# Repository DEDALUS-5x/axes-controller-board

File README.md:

# Axes Controller Board (ACB)

KiCad design files of the Axes Controller Board, the STM32H723-based motion
controller of the [DEDALUS](https://dedalus-5x.github.io/dedalus-docs/)
five-axis printer. The board drives two brushed DC servo axes through
external H-bridges and six stepper drivers in StepStick sockets, reads
differential incremental and SPI absolute encoders, and carries a
Raspberry Pi 5 as a daughterboard.

Current revision: 1.1.0 (see [Revision history](#revision-history)).

Firmware: <https://github.com/DEDALUS-5x/axes-controller-fw>

## Contents

| File | Description |
| --- | --- |
| `axes-controller-board.kicad_pro` | KiCad 8 project |
| `axes-controller-board.kicad_sch`, `mcu.kicad_sch`, `sensors.kicad_sch` | Schematics (root, MCU, sensors) |
| `axes-controller-board.kicad_pcb` | Four-layer layout, 203 x 108 mm, 1.6 mm |
| `libs/footprints.pretty/` | Footprints that can be redistributed with the design |
| `sym-lib-table` | Project symbol libraries (third-party, see below) |
| `outputs/ACB_schematic.pdf` | Schematic, PDF |
| `outputs/ACB_gerbers.zip` | Gerber and Excellon drill files (four layers) |
| `outputs/ACB_bom.csv` | BOM of the SMT-assembled parts, with LCSC codes |
| `outputs/ACB_positions.csv` | Placement of the SMT-assembled parts (top side, mm) |

The files in `outputs/` were exported from the KiCad project with `kicad-cli`
(KiCad 9). For JLCPCB assembly, the
[Fabrication Toolkit](https://github.com/bennymeg/Fabrication-Toolkit) plug-in
generates the BOM and placement files in the required format, using the LCSC
codes and rotation offsets stored in the schematic.

## Third-party library parts

The symbols, footprints and 3D models of the parts below are SamacSys ECAD
models or vendor models. Their terms allow using them in board designs
without restriction, but not redistributing them as library components, so
they are not included in this repository.

The schematics and the PCB embed a copy of every symbol and footprint they
use: the project opens and fabrication outputs can be generated without these
libraries. Download them only to edit the parts, free of charge, and place them
at the paths below, which match `sym-lib-table` and the footprint names in the
layout.

| Part | Use | Expected location | Source |
| --- | --- | --- | --- |
| STM32H723ZGT6 | IC5, microcontroller | `libs/STM32H7/STM32H723ZGT6/` | [Component Search Engine](https://componentsearchengine.com) (SamacSys) |
| TPS5450QDDARQ1 | IC1, 5 V buck converter | `libs/TPS5450/` | [Component Search Engine](https://componentsearchengine.com) (SamacSys) |
| ACS37800KMACTR-030B3-SPI | IC2, IC3, current monitors (optional) | `libs/ACS/` | [Component Search Engine](https://componentsearchengine.com) (SamacSys) |
| Phoenix Contact 1985205, 1985234, 1985250 | Terminal blocks | `libs/morsetto/`, `libs/footprints.pretty/`, `libs/3dmodels/` | [Component Search Engine](https://componentsearchengine.com) (SamacSys) |
| Samtec FTSH-107-01-L-DV-K-TR | J1, STDC14 debug connector | `libs/footprints.pretty/` | [Samtec](https://www.samtec.com) |
| Raspberry Pi 4 Model B | 3D model only | `libs/3dmodels/` | [Raspberry Pi Ltd](https://www.raspberrypi.com) |

## Revision history

### 1.1.0

The layout matches the firmware
([axes-controller-fw](https://github.com/DEDALUS-5x/axes-controller-fw)):
no hand modifications are needed.

- The STEP lines of five driver sockets go to timer outputs, so that steps are
  generated in hardware: Z1 on PB9 (TIM17 CH1), Z2 on PB5 (TIM3 CH2), A1 on PC12
  (TIM15 CH1), A2 on PB6 (TIM16 CH1N), C on PC7 (TIM8 CH2). The 33 ohm series
  resistors are kept; R19 and R23 moved next to the new routes, R4 took the
  place of R27.
- The Raspberry Pi chip select (J27 pin 24) goes to PA4, the hardware NSS of
  SPI3.
- The third DC-servo channel is removed (terminal J4, resistors R27 and R28),
  together with its current monitor IC4, capacitor C39 and supply terminal J30.
- New connector J47 (1x8, 2.54 mm) for an SPI absolute encoder on SPI4, chip
  select PC15. Same pinout as J31 and J32: 1-2 3V3, 3 not connected, 4 CS,
  5 SCK, 6 MOSI, 7 MISO, 8 GND.
- Spare header J5: pins 6 and 7 are no longer connected (PB5 and PB6 are STEP
  lines now); six spare I/O remain.

### 1.0.0 (prototype)

On the 1.0.0 board the following signals must be re-routed with wires, because
the STEP lines of five driver sockets reach pins without timer outputs and the
Raspberry Pi chip select reaches a pin without the SPI3 hardware NSS function.
The firmware uses the re-routed pins. On this revision the third DC-servo
channel loses one PWM line (PC7 is used for STEP C).

| Signal | Destination | Routed to | Re-routed to |
| --- | --- | --- | --- |
| STEP Z1 | J9 pin 7 | PE0 | PB9 (TIM17 CH1) |
| STEP Z2 | J12 pin 7 | PE3 | PB5 (TIM3 CH2), J5 pin 7 |
| STEP A1 | J15 pin 7 | PD0 | PC12 (TIM15 CH1) |
| STEP A2 | J18 pin 7 | PD3 | PB6 (TIM16 CH1N), J5 pin 6 |
| STEP C | J21 pin 7 | PD11 | PC7 (TIM8 CH2), J4 pin 2 |
| Raspberry Pi CE0 | J27 pin 24 | PB1 | PA4 (SPI3 NSS) |

## License

Copyright 2026 Leonardo Pasquato.

This source describes Open Hardware and is licensed under the CERN-OHL-S v2.

You may redistribute and modify this source and make products using it under
the terms of the CERN-OHL-S v2 (<https://ohwr.org/cern_ohl_s_v2.txt>).

This source is distributed WITHOUT ANY EXPRESS OR IMPLIED WARRANTY,
INCLUDING OF MERCHANTABILITY, SATISFACTORY QUALITY AND FITNESS FOR A
PARTICULAR PURPOSE. Please see the CERN-OHL-S v2 for applicable conditions.

Source location: <https://github.com/DEDALUS-5x/axes-controller-board>

As per CERN-OHL-S v2 section 4, should You produce hardware based on this
source, You must where practicable maintain the Source Location visible on
the external case of the Gizmo or other products you make using this source.

Exceptions: `libs/footprints.pretty/MountingHole_3.2mm_M3_ISO14580.kicad_mod`
and `libs/footprints.pretty/raspberrypi.kicad_mod` are derived from the
[KiCad libraries](https://www.kicad.org/libraries/license/) and remain under
CC-BY-SA 4.0 with the KiCad library exception.

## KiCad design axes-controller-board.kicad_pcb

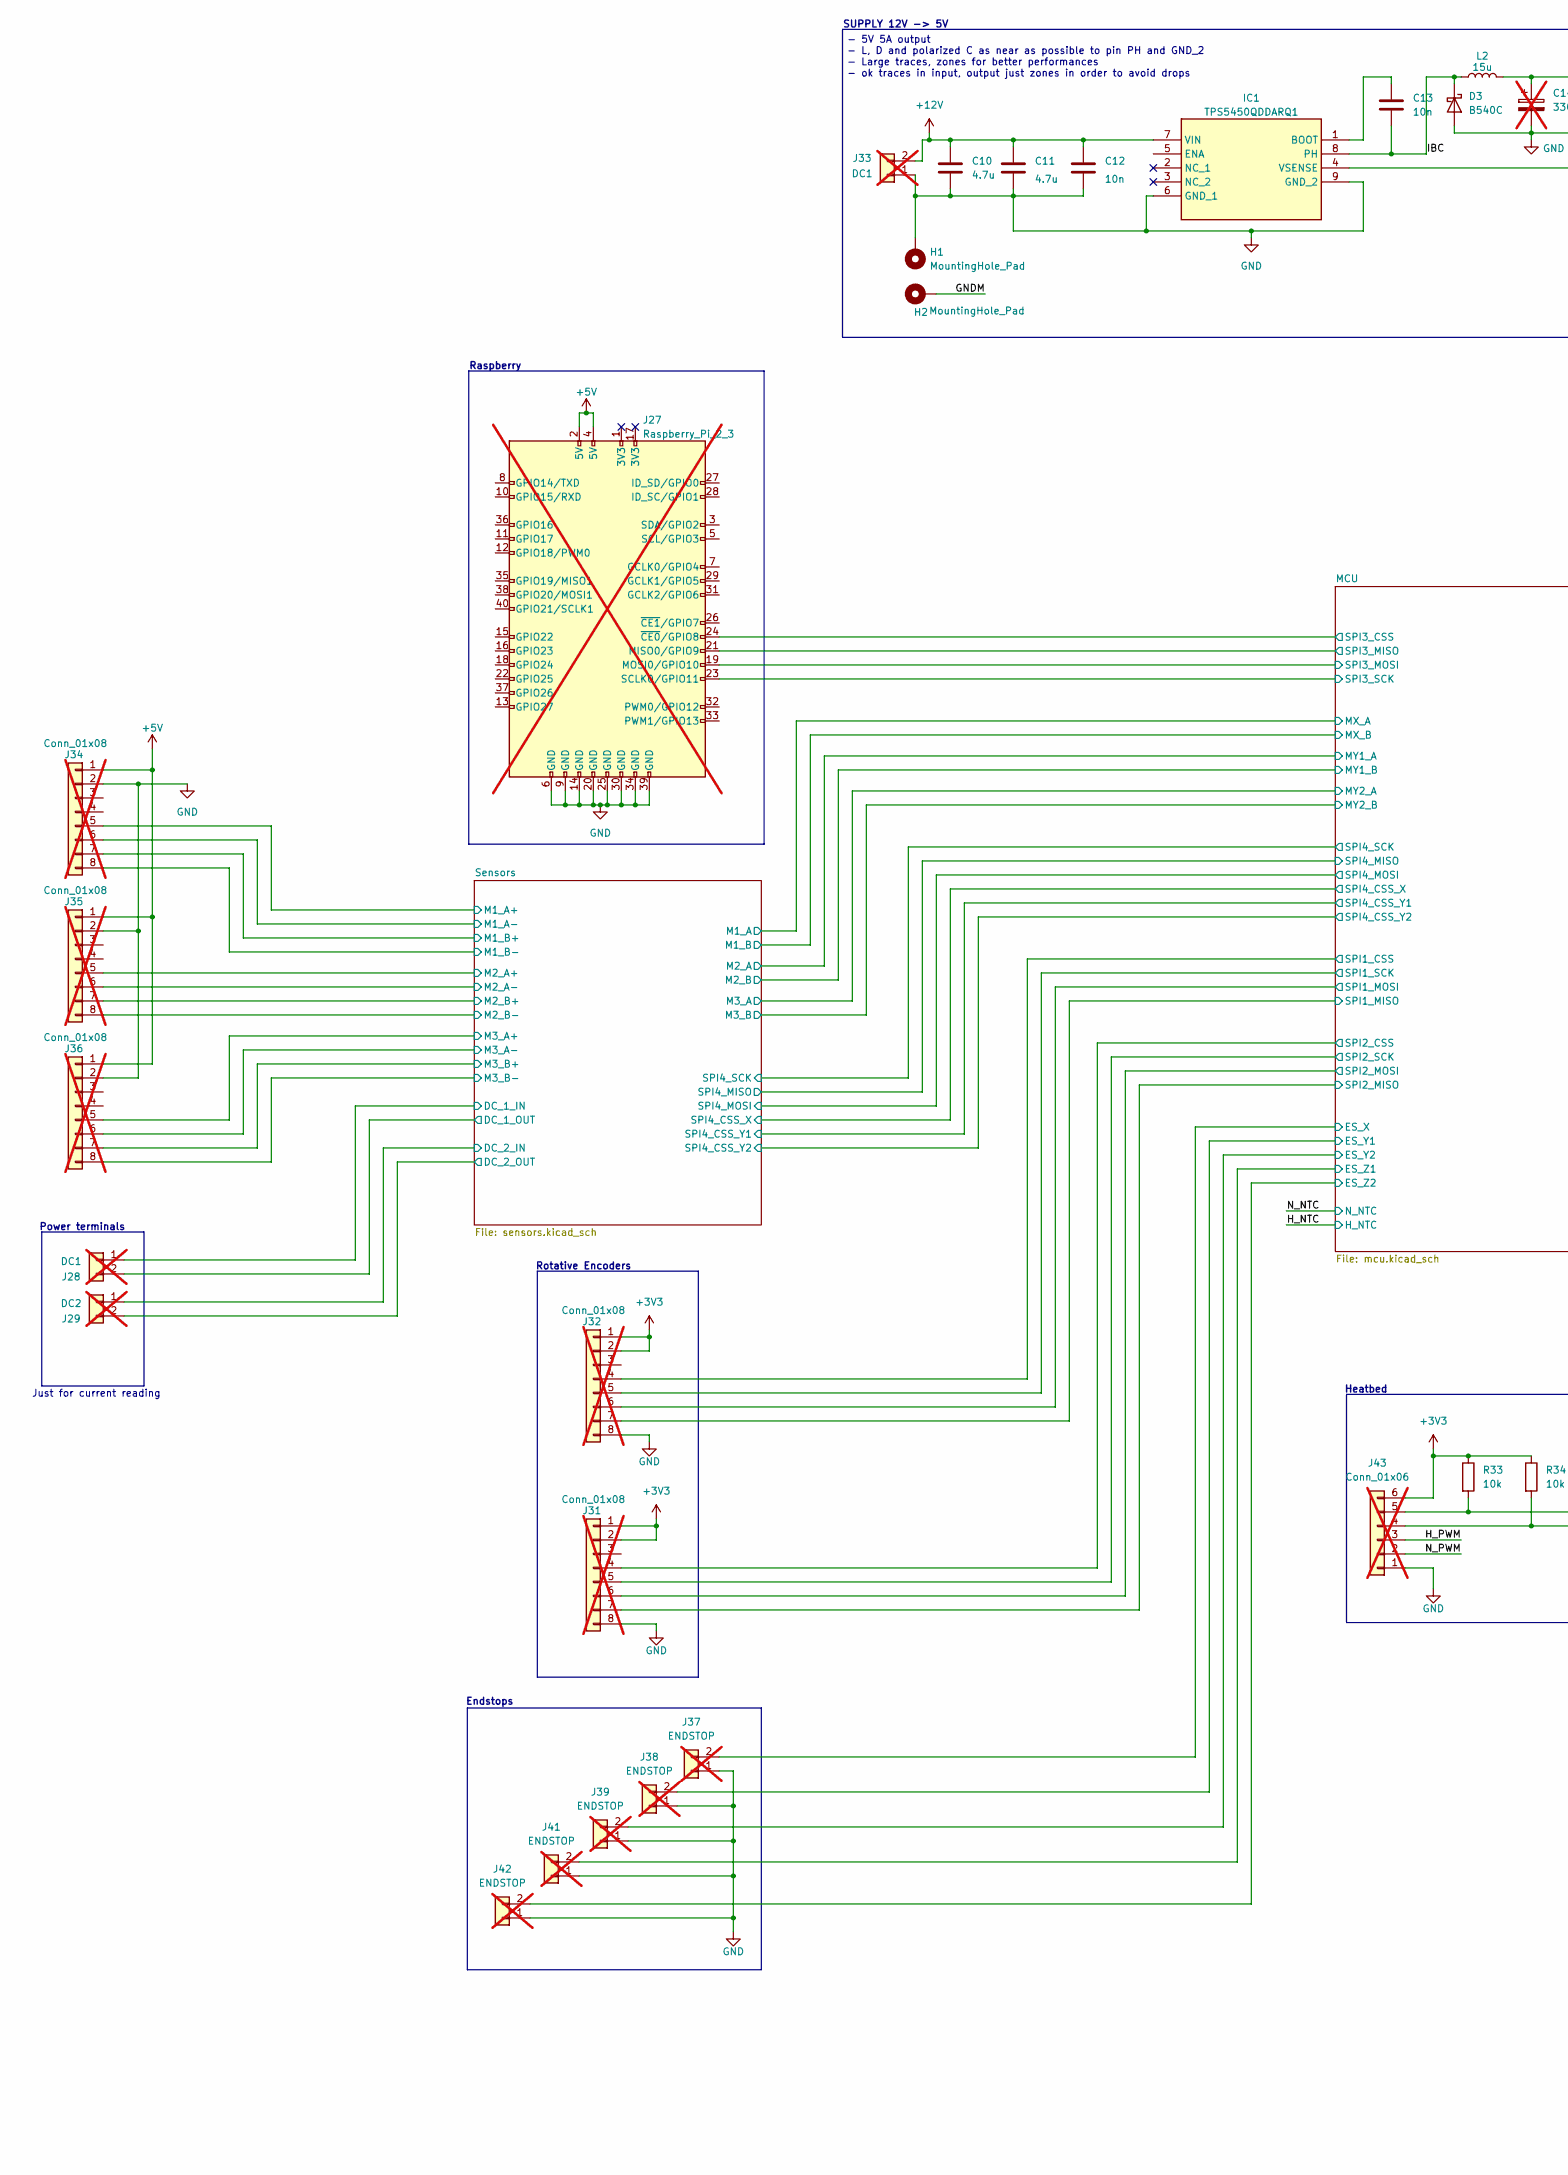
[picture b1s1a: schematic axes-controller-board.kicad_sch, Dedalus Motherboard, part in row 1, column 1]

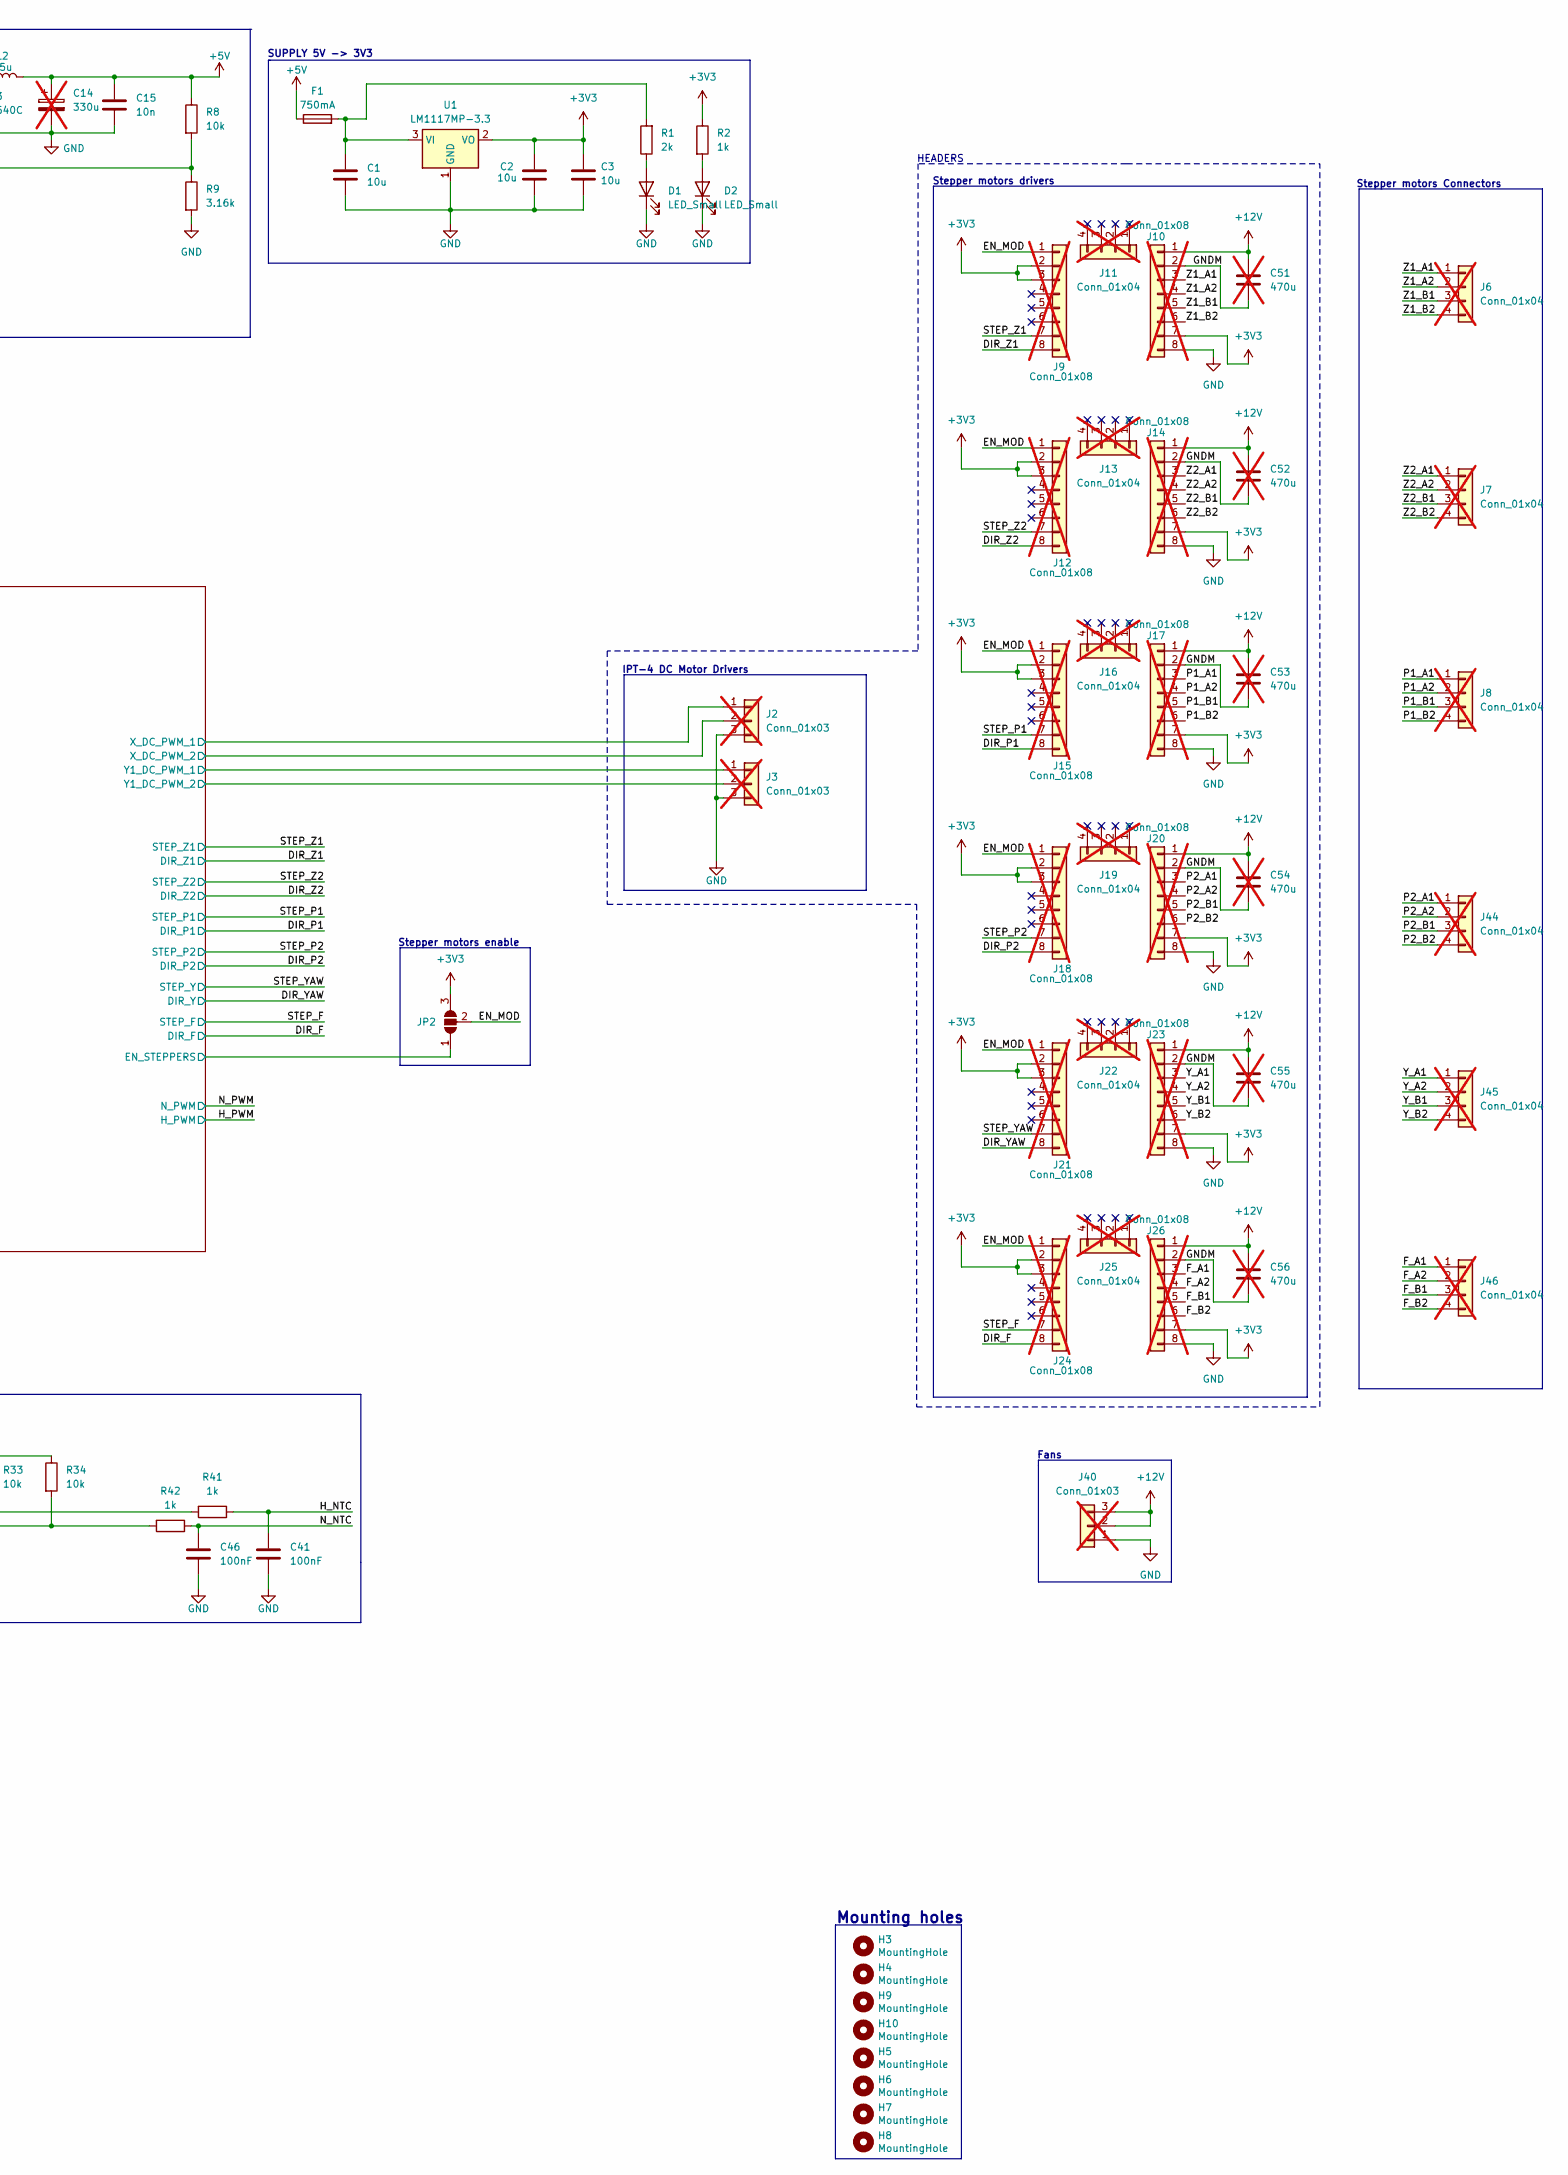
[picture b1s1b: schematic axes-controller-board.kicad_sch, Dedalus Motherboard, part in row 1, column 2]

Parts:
C1, C2, C3: 10u; C_0603_1608Metric; LCSC C19702
C10, C11: 4.7u; C_0805_2012Metric; LCSC C1779
C12, C13, C15: 10n; C_0603_1608Metric; LCSC C57112
C14: 330u; CP_Radial_D10.0mm_P5.00mm; not fitted
C41, C46: 100nF; C_0603_1608Metric; LCSC C14663
C51, C52, C53, C54, C55, C56: 470u; PinHeader_1x02_P1.00mm_Vertical; not fitted
D1, D2: LED_Small; D_0603_1608Metric; MPN TLMS1000-GS15; LCSC C2286
D3: B540C; D_SMC_Handsoldering; LCSC C72264
F1: 750mA; Fuse_0603_1608Metric; LCSC C206991
H1, H2: MountingHole_Pad; TestPoint_GNDedge
H3, H4, H5, H6, H7, H8, H9, H10: MountingHole; MountingHole_3.2mm_M3_ISO14580
IC1: TPS5450QDDARQ1; SOIC127P600X170-9N; Mouser Part Number 595-TPS5450QDDARQ1
J2, J3, J40: Conn_01x03; 1985205; not fitted
J6, J7, J8, J44, J45, J46: Conn_01x04; JST_XH_B4B-XH-A_1x04_P2.50mm_Vertical; not fitted
J9, J10, J12, J14, J15, J17, J18, J20, J21, J23, J24, J26: Conn_01x08; PinHeader_1x08_P2.54mm_Vertical; not fitted
J11, J13, J16, J19, J22, J25: Conn_01x04; PinHeader_1x04_P2.54mm_Vertical; not fitted
J27: Raspberry_Pi_2_3; raspberrypi; MPN 2.54-2*20; LCSC C2977589; not fitted
J28, J33: DC1; TerminalBlock_Phoenix_MKDS-1,5-2-5.08_1x02_P5.08mm_Horizont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; not fitted
J29: DC2; TerminalBlock_Phoenix_MKDS-1,5-2-5.08_1x02_P5.08mm_Horizont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; not fitted
J31, J32, J34, J35, J36: Conn_01x08; 1985250; not fitted
J37, J38, J39, J41, J42: ENDSTOP; PinHeader_1x02_P2.54mm_Vertical; not fitted
J43: Conn_01x06; 1985234; not fitted
JP2: SolderJumper_3_Open; SolderJumper-3_P1.3mm_Open_RoundedPad1.0x1.5mm
L2: 15u; L_12x12mm_H6mm; LCSC C2847584
R1: 2k; R_0603_1608Metric; LCSC C22975
R2, R41, R42: 1k; R_0603_1608Metric; LCSC C21190
R8, R33, R34: 10k; R_0603_1608Metric; LCSC C25804
R9: 3.16k; R_0603_1608Metric; LCSC C100959
U1: LM1117MP-3.3; SOT-223-3_TabPin2; MPN LM1117MP-3.3/TR; LCSC C498153

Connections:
+3V3: C2.1, C3.1, J9.2, J9.3, J10.7, J12.2, J12.3, J14.7, J15.2, J15.3, J17.7, J18.2, J18.3, J20.7, J21.2, J21.3, J23.7, J24.2, J24.3, J26.7, J31.1, J31.2, J32.1, J32.2, J43.6, JP2.3 (B), R2.1, R33.1, R34.1, U1.2 (VO); also elsewhere on the board
+5V: C14.1, C15.1, F1.1, J27.2 (5V), J27.4 (5V), J34.1, J35.1, J36.1, L2.2, R8.1; also elsewhere on the board
+12V: C10.1, C11.1, C12.1, C51.1, C52.1, C53.1, C54.1, C55.1, C56.1, IC1.7 (VIN), J10.1, J14.1, J17.1, J20.1, J23.1, J26.1, J33.2, J40.2, J40.3
/DIR_F: J24.8; also elsewhere on the board
/DIR_P1: J15.8; also elsewhere on the board
/DIR_P2: J18.8; also elsewhere on the board
/DIR_YAW: J21.8; also elsewhere on the board
/DIR_Z1: J9.8; also elsewhere on the board
/DIR_Z2: J12.8; also elsewhere on the board
/EN_MOD: J9.1, J12.1, J15.1, J18.1, J21.1, J24.1, JP2.2 (C)
/F_A1: J26.3, J46.1
/F_A2: J26.4, J46.2
/F_B1: J26.5, J46.3
/F_B2: J26.6, J46.4
/GNDM: C51.2, C52.2, C53.2, C54.2, C55.2, C56.2, H2.1, J10.2, J14.2, J17.2, J20.2, J23.2, J26.2
/H_NTC: C41.1, R41.1; also elsewhere on the board
/H_PWM: J43.3; also elsewhere on the board
/IBC: C13.1, D3.1 (K), IC1.8 (PH), L2.1
/MCU/EN_STEPPERS: JP2.1 (A); also elsewhere on the board
/MCU/ES_X: J37.2; also elsewhere on the board
/MCU/ES_Y1: J38.2; also elsewhere on the board
/MCU/ES_Y2: J39.2; also elsewhere on the board
/MCU/ES_Z1: J41.2; also elsewhere on the board
/MCU/ES_Z2: J42.2; also elsewhere on the board
/MCU/SPI1_CSS: J32.4; also elsewhere on the board
/MCU/SPI1_MISO: J32.7; also elsewhere on the board
/MCU/SPI1_MOSI: J32.6; also elsewhere on the board
/MCU/SPI1_SCK: J32.5; also elsewhere on the board
/MCU/SPI2_CSS: J31.4; also elsewhere on the board
/MCU/SPI2_MISO: J31.7; also elsewhere on the board
/MCU/SPI2_MOSI: J31.6; also elsewhere on the board
/MCU/SPI2_SCK: J31.5; also elsewhere on the board
/MCU/SPI3_CSS: J27.24 (~CE0/GPIO8); also elsewhere on the board
/MCU/SPI3_MISO: J27.21 (MISO0/GPIO9); also elsewhere on the board
/MCU/SPI3_MOSI: J27.19 (MOSI0/GPIO10); also elsewhere on the board
/MCU/SPI3_SCK: J27.23 (SCLK0/GPIO11); also elsewhere on the board
/MCU/X_DC_PWM_1: J2.1; also elsewhere on the board
/MCU/X_DC_PWM_2: J2.2; also elsewhere on the board
/MCU/Y1_DC_PWM_1: J3.1; also elsewhere on the board
/MCU/Y1_DC_PWM_2: J3.2; also elsewhere on the board
/N_NTC: C46.1, R42.1; also elsewhere on the board
/N_PWM: J43.2; also elsewhere on the board
/P1_A1: J8.1, J17.3
/P1_A2: J8.2, J17.4
/P1_B1: J8.3, J17.5
/P1_B2: J8.4, J17.6
/P2_A1: J20.3, J44.1
/P2_A2: J20.4, J44.2
/P2_B1: J20.5, J44.3
/P2_B2: J20.6, J44.4
/STEP_F: J24.7; also elsewhere on the board
/STEP_P1: J15.7; also elsewhere on the board
/STEP_P2: J18.7; also elsewhere on the board
/STEP_YAW: J21.7; also elsewhere on the board
/STEP_Z1: J9.7; also elsewhere on the board
/STEP_Z2: J12.7; also elsewhere on the board
/Sensors/DC_1_IN: J28.1; also elsewhere on the board
/Sensors/DC_1_OUT: J28.2; also elsewhere on the board
/Sensors/DC_2_IN: J29.1; also elsewhere on the board
/Sensors/DC_2_OUT: J29.2; also elsewhere on the board
/Sensors/M1_A+: J34.5; also elsewhere on the board
/Sensors/M1_A-: J34.6; also elsewhere on the board
/Sensors/M1_B+: J34.7; also elsewhere on the board
/Sensors/M1_B-: J34.8; also elsewhere on the board
/Sensors/M2_A+: J35.5; also elsewhere on the board
/Sensors/M2_A-: J35.6; also elsewhere on the board
/Sensors/M2_B+: J35.7; also elsewhere on the board
/Sensors/M2_B-: J35.8; also elsewhere on the board
/Sensors/M3_A+: J36.5; also elsewhere on the board
/Sensors/M3_A-: J36.6; also elsewhere on the board
/Sensors/M3_B+: J36.7; also elsewhere on the board
/Sensors/M3_B-: J36.8; also elsewhere on the board
/Y_A1: J23.3, J45.1
/Y_A2: J23.4, J45.2
/Y_B1: J23.5, J45.3
/Y_B2: J23.6, J45.4
/Z1_A1: J6.1, J10.3
/Z1_A2: J6.2, J10.4
/Z1_B1: J6.3, J10.5
/Z1_B2: J6.4, J10.6
/Z2_A1: J7.1, J14.3
/Z2_A2: J7.2, J14.4
/Z2_B1: J7.3, J14.5
/Z2_B2: J7.4, J14.6
GND: C1.2, C2.2, C3.2, C10.2, C11.2, C12.2, C14.2, C15.2, C41.2, C46.2, D1.1 (K), D2.1 (K), D3.2 (A), H1.1, IC1.6 (GND_1), IC1.9 (GND_2), J2.3, J3.3, J10.8, J14.8, J17.8, J20.8, J23.8, J26.8, J27.6 (GND), J27.9 (GND), J27.14 (GND), J27.20 (GND), J27.25 (GND), J27.30 (GND), J27.34 (GND), J27.39 (GND), J31.8, J32.8, J33.1, J34.2, J35.2, J36.2, J37.1, J38.1, J39.1, J40.1, J41.1, J42.1, J43.1, R9.2, U1.1 (GND); also elsewhere on the board
unnamed: D1.2 (A), R1.1
unnamed: D2.2 (A), R2.2
unnamed: C13.2, IC1.1 (BOOT)
unnamed: IC1.4 (VSENSE), R8.2, R9.1
unnamed: J43.4, R34.2, R42.2
unnamed: J43.5, R33.2, R41.2
unnamed: C1.1, F1.2, R1.2, U1.3 (VI)

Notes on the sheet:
Stepper motors Connectors
Just for current reading
SUPPLY 12V -> 5V
Stepper motors drivers
Fans
Heatbed
Mounting holes
IPT-4 DC Motor Drivers
SUPPLY 5V -> 3V3
HEADERS
Raspberry
Power terminals
Endstops
Rotative Encoders
- 5V 5A output - L, D and polarized C as near as possible to pin PH and GND_2 - Large traces, zones for better performances - ok traces in input, output just zones in order to avoid drops
Stepper motors enable

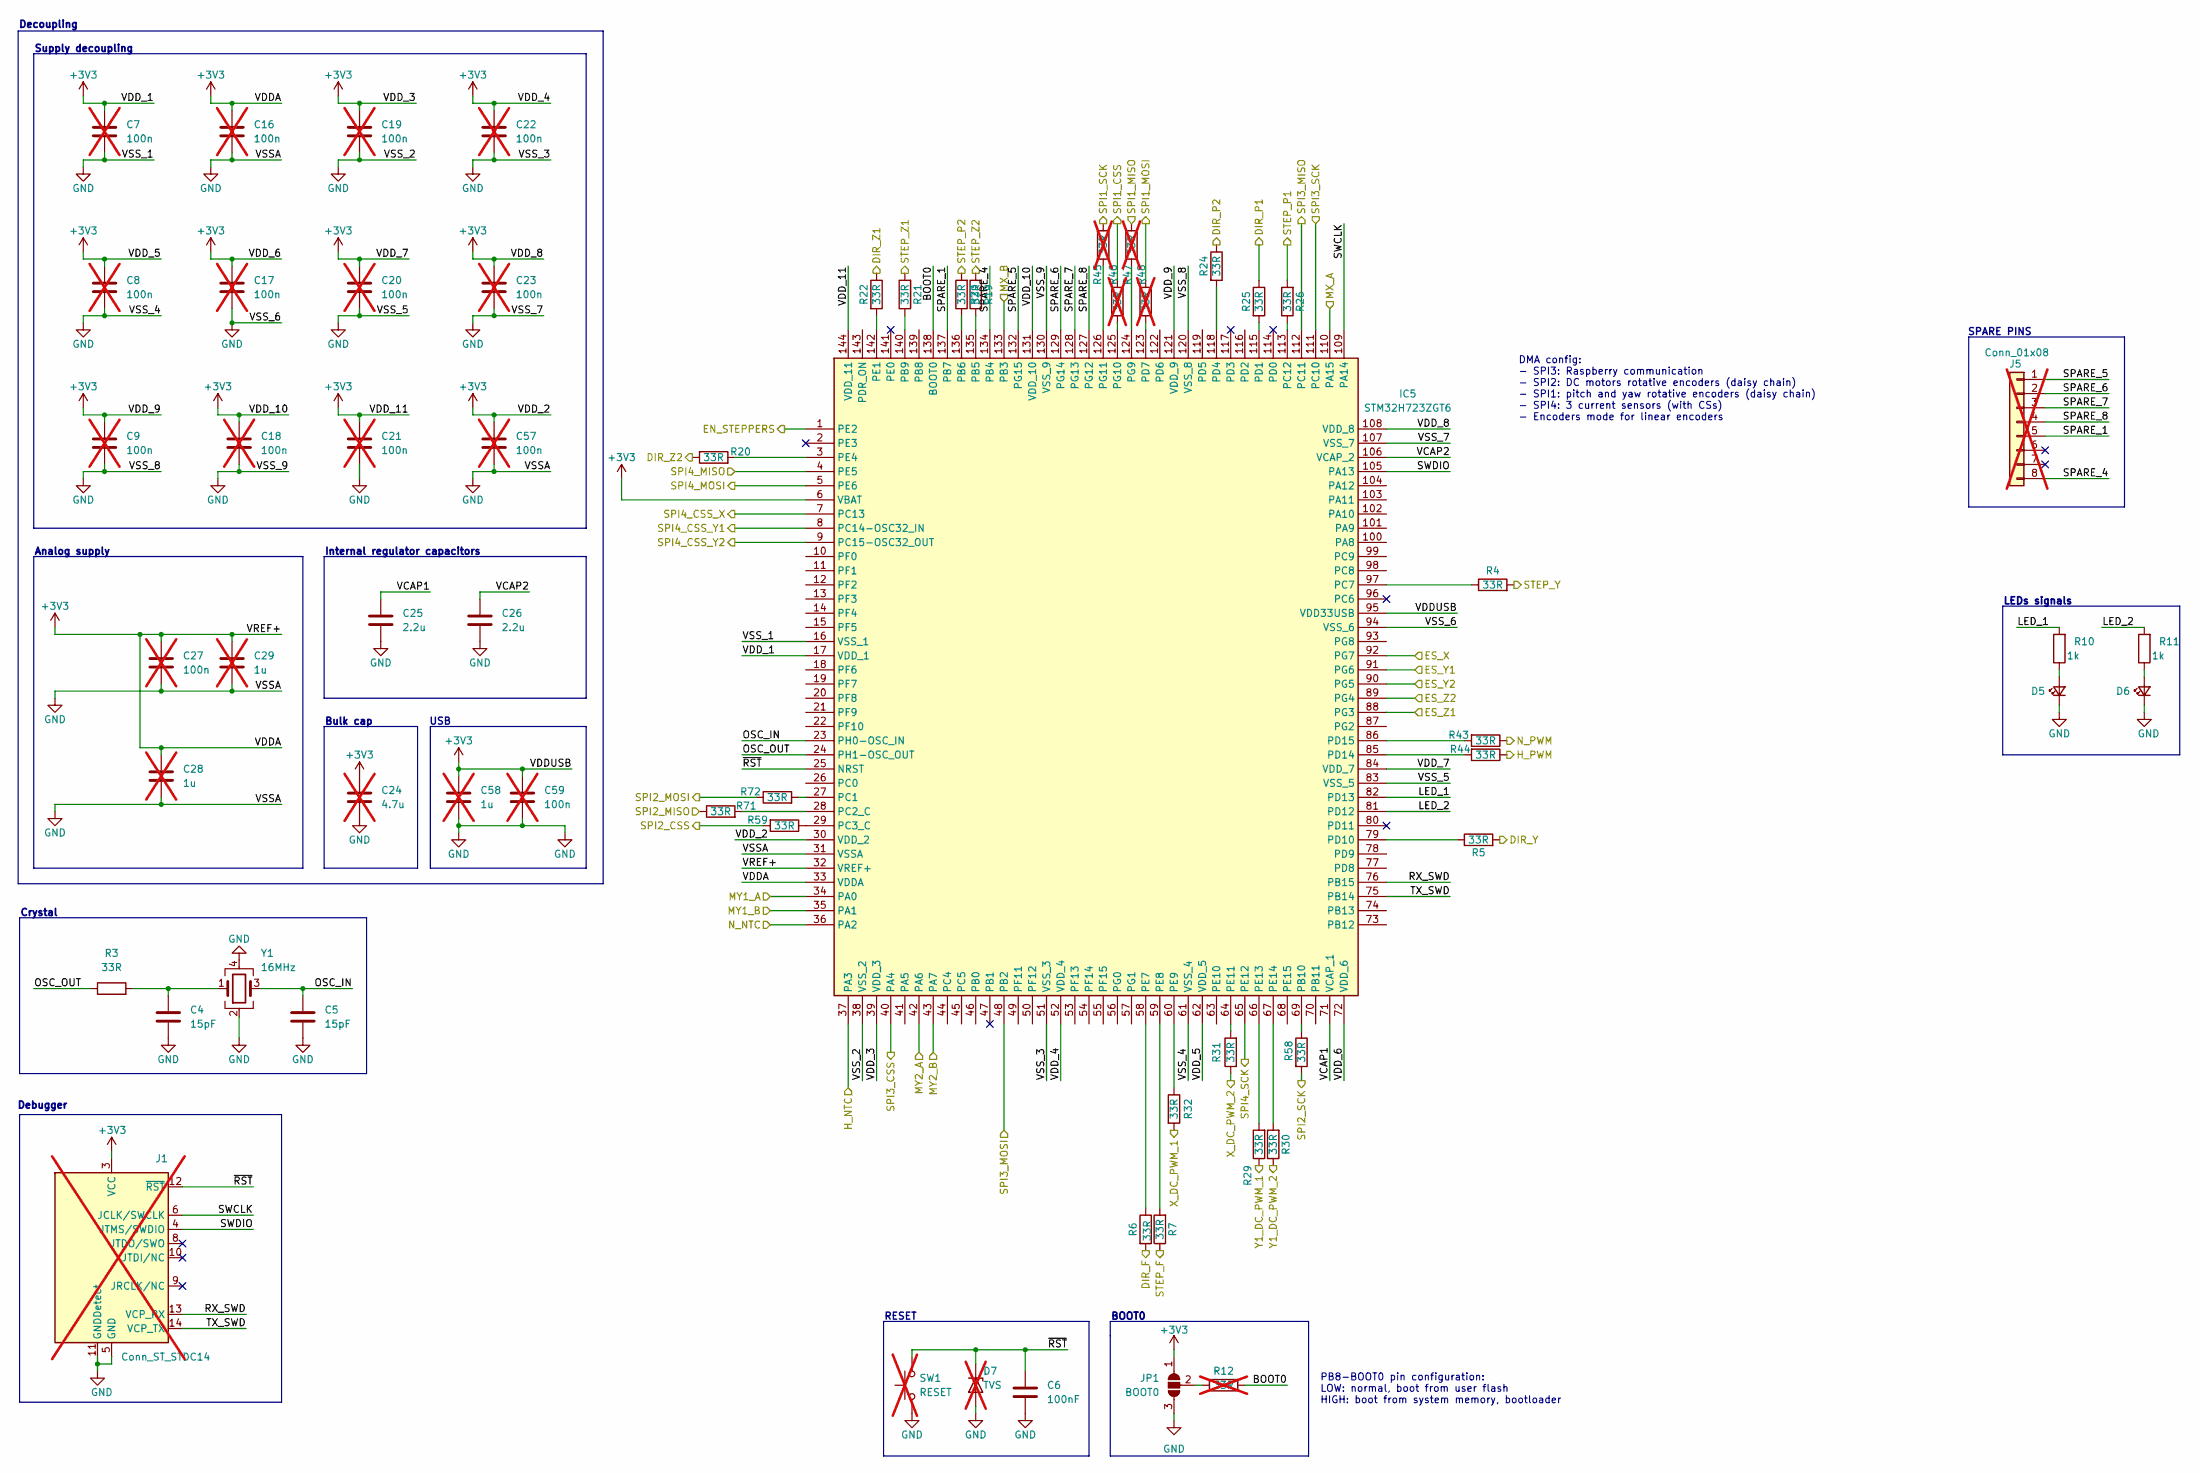
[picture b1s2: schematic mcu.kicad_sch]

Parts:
C4, C5: 15pF; C_0603_1608Metric; LCSC C1644
C6: 100nF; C_0603_1608Metric; LCSC C14663
C7, C8, C9, C16, C17, C18, C19, C20, C21, C22, C23, C27, C57, C59: 100n; C_0603_1608Metric; not fitted
C24: 4.7u; C_0805_2012Metric; not fitted
C25, C26: 2.2u; C_0805_2012Metric; LCSC C377773
C28, C29, C58: 1u; C_0805_2012Metric; not fitted
D5, D6: LED_Small; LED_0603_1608Metric; LCSC C2286
D7: TVS; D_SOD-523; not fitted
IC5: STM32H723ZGT6; QFP50P2200X2200X160-144N; Mouser Part Number 511-STM32H723ZGT6
J1: Conn_ST_STDC14; SAMTEC_FTSH-107-01-L-DV-K-TR; not fitted
J5: Conn_01x08; PinHeader_1x08_P2.54mm_Vertical; not fitted
JP1: BOOT0; SolderJumper-3_P1.3mm_Open_RoundedPad1.0x1.5mm
R3, R4, R5, R6, R7, R19, R20, R21, R22, R23, R24, R25, R26, R29, R30, R31, R32, R43, R44, R58, R59, R71, R72: 33R; R_0603_1608Metric; LCSC C23140
R10, R11: 1k; R_0603_1608Metric; LCSC C21190
R12: 33R; R_0603_1608Metric; not fitted
R45, R46, R47, R48: 33R; R_0603_1608Metric; LCSC C23140; not fitted
SW1: RESET; SW_SPST_FSMSM; not fitted
Y1: 16MHz; Crystal_SMD_EuroQuartz_MT-4Pin_3.2x2.5mm; LCSC C27869

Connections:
+3V3: C7.1, C8.1, C9.1, C16.1, C17.1, C18.1, C19.1, C20.1, C21.1, C22.1, C23.1, C24.1, C27.1, C28.1, C29.1, C57.1, C58.1, C59.1, IC5.6 (VBAT), IC5.17 (VDD_1), IC5.30 (VDD_2), IC5.32 (VREF+), IC5.33 (VDDA), IC5.39 (VDD_3), IC5.52 (VDD_4), IC5.62 (VDD_5), IC5.72 (VDD_6), IC5.84 (VDD_7), IC5.95 (VDD33USB), IC5.108 (VDD_8), IC5.121 (VDD_9), IC5.131 (VDD_10), IC5.144 (VDD_11), J1.3 (VCC), JP1.1 (A); also elsewhere on the board
/DIR_F: R6.2; also elsewhere on the board
/DIR_P1: R25.1; also elsewhere on the board
/DIR_P2: R24.1; also elsewhere on the board
/DIR_YAW: R5.2; also elsewhere on the board
/DIR_Z1: R22.1; also elsewhere on the board
/DIR_Z2: R20.1; also elsewhere on the board
/H_NTC: IC5.37 (PA3); also elsewhere on the board
/H_PWM: R44.1; also elsewhere on the board
/MCU/BOOT0: IC5.138 (BOOT0), R12.2
/MCU/EN_STEPPERS: IC5.1 (PE2); also elsewhere on the board
/MCU/ES_X: IC5.92 (PG7); also elsewhere on the board
/MCU/ES_Y1: IC5.91 (PG6); also elsewhere on the board
/MCU/ES_Y2: IC5.90 (PG5); also elsewhere on the board
/MCU/ES_Z1: IC5.88 (PG3); also elsewhere on the board
/MCU/ES_Z2: IC5.89 (PG4); also elsewhere on the board
/MCU/LED_1: IC5.82 (PD13), R10.2
/MCU/LED_2: IC5.81 (PD12), R11.2
/MCU/MX_A: IC5.110 (PA15); also elsewhere on the board
/MCU/MX_B: IC5.133 (PB3); also elsewhere on the board
/MCU/MY1_A: IC5.34 (PA0); also elsewhere on the board
/MCU/MY1_B: IC5.35 (PA1); also elsewhere on the board
/MCU/MY2_A: IC5.42 (PA6); also elsewhere on the board
/MCU/MY2_B: IC5.43 (PA7); also elsewhere on the board
/MCU/OSC_IN: C5.1, IC5.23 (PH0-OSC_IN), Y1.3
/MCU/OSC_OUT: IC5.24 (PH1-OSC_OUT), R3.1
/MCU/RX_SWD: IC5.76 (PB15), J1.13 (VCP_RX)
/MCU/SPARE_1: IC5.137 (PB7), J5.5
/MCU/SPARE_4: IC5.134 (PB4), J5.8
/MCU/SPARE_5: IC5.132 (PG15), J5.1
/MCU/SPARE_6: IC5.129 (PG14), J5.2
/MCU/SPARE_7: IC5.128 (PG13), J5.3
/MCU/SPARE_8: IC5.127 (PG12), J5.4
/MCU/SPI1_CSS: R46.1; also elsewhere on the board
/MCU/SPI1_MISO: R47.1; also elsewhere on the board
/MCU/SPI1_MOSI: R48.1; also elsewhere on the board
/MCU/SPI1_SCK: R45.1; also elsewhere on the board
/MCU/SPI2_CSS: R59.2; also elsewhere on the board
/MCU/SPI2_MISO: R71.1; also elsewhere on the board
/MCU/SPI2_MOSI: R72.1; also elsewhere on the board
/MCU/SPI2_SCK: R58.2; also elsewhere on the board
/MCU/SPI3_CSS: IC5.40 (PA4); also elsewhere on the board
/MCU/SPI3_MISO: IC5.112 (PC11); also elsewhere on the board
/MCU/SPI3_MOSI: IC5.48 (PB2); also elsewhere on the board
/MCU/SPI3_SCK: IC5.111 (PC10); also elsewhere on the board
/MCU/SPI4_CSS_X: IC5.7 (PC13); also elsewhere on the board
/MCU/SPI4_CSS_Y1: IC5.8 (PC14-OSC32_IN); also elsewhere on the board
/MCU/SPI4_CSS_Y2: IC5.9 (PC15-OSC32_OUT); also elsewhere on the board
/MCU/SWCLK: IC5.109 (PA14), J1.6 (JCLK/SWCLK)
/MCU/SWDIO: IC5.105 (PA13), J1.4 (JTMS/SWDIO)
/MCU/TX_SWD: IC5.75 (PB14), J1.14 (VCP_TX)
/MCU/VCAP1: C25.1, IC5.71 (VCAP_1)
/MCU/VCAP2: C26.1, IC5.106 (VCAP_2)
/MCU/X_DC_PWM_1: R32.2; also elsewhere on the board
/MCU/X_DC_PWM_2: R31.1; also elsewhere on the board
/MCU/Y1_DC_PWM_1: R29.1; also elsewhere on the board
/MCU/Y1_DC_PWM_2: R30.1; also elsewhere on the board
/MCU/~RST: C6.1, D7.1 (K), IC5.25 (NRST), J1.12 (~RST), SW1.2
/N_NTC: IC5.36 (PA2); also elsewhere on the board
/N_PWM: R43.1; also elsewhere on the board
/STEP_F: R7.1; also elsewhere on the board
/STEP_P1: R26.2; also elsewhere on the board
/STEP_P2: R23.2; also elsewhere on the board
/STEP_YAW: R4.2; also elsewhere on the board
/STEP_Z1: R21.2; also elsewhere on the board
/STEP_Z2: R19.2; also elsewhere on the board
/Sensors/SPI4_MISO: IC5.4 (PE5); also elsewhere on the board
/Sensors/SPI4_MOSI: IC5.5 (PE6); also elsewhere on the board
/Sensors/SPI4_SCK: IC5.65 (PE12); also elsewhere on the board
GND: C4.2, C5.2, C6.2, C7.2, C8.2, C9.2, C16.2, C17.2, C18.2, C19.2, C20.2, C21.2, C22.2, C23.2, C24.2, C25.2, C26.2, C27.2, C28.2, C29.2, C57.2, C58.2, C59.2, D5.1 (K), D6.1 (K), D7.2 (A), IC5.16 (VSS_1), IC5.31 (VSSA), IC5.38 (VSS_2), IC5.51 (VSS_3), IC5.61 (VSS_4), IC5.83 (VSS_5), IC5.94 (VSS_6), IC5.107 (VSS_7), IC5.120 (VSS_8), IC5.130 (VSS_9), J1.5 (GND), J1.7 (GND), J1.11 (GNDDetect), JP1.3 (B), SW1.1, Y1.2, Y1.4; also elsewhere on the board
unnamed: C4.1, R3.2, Y1.1
unnamed: D5.2 (A), R10.1
unnamed: D6.2 (A), R11.1
unnamed: IC5.135 (PB5), R19.1
unnamed: IC5.136 (PB6), R23.1
unnamed: IC5.140 (PB9), R21.1
unnamed: IC5.69 (PB10), R58.1
unnamed: IC5.27 (PC1), R72.2
unnamed: IC5.28 (PC2_C), R71.2
unnamed: IC5.29 (PC3_C), R59.1
unnamed: IC5.97 (PC7), R4.1
unnamed: IC5.113 (PC12), R26.1
unnamed: IC5.115 (PD1), R25.2
unnamed: IC5.118 (PD4), R24.2
unnamed: IC5.123 (PD7), R48.2
unnamed: IC5.79 (PD10), R5.1
unnamed: IC5.85 (PD14), R44.2
unnamed: IC5.86 (PD15), R43.2
unnamed: IC5.142 (PE1), R22.2
unnamed: IC5.3 (PE4), R20.2
unnamed: IC5.58 (PE7), R6.1
unnamed: IC5.59 (PE8), R7.2
unnamed: IC5.60 (PE9), R32.1
unnamed: IC5.64 (PE11), R31.2
unnamed: IC5.66 (PE13), R29.2
unnamed: IC5.67 (PE14), R30.2
unnamed: IC5.124 (PG9), R47.2
unnamed: IC5.125 (PG10), R46.2
unnamed: IC5.126 (PG11), R45.2
unnamed: JP1.2 (C), R12.1

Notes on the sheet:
Decoupling
Debugger
SPARE PINS
Crystal
Bulk cap
LEDs signals
DMA config: - SPI3: Raspberry communication - SPI2: DC motors rotative encoders (daisy chain) - SPI1: pitch and yaw rotative encoders (daisy chain) - SPI4: 3 current sensors (with CSs) - Encoders mode for linear encoders
PB8-BOOT0 pin configuration: LOW: normal, boot from user flash HIGH: boot from system memory, bootloader
Supply decoupling
USB
Internal regulator capacitors
Analog supply
BOOT0
RESET

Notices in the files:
axes-controller-board.kicad_pcb:
Licensed under CERN-OHL-S-2.0, https://ohwr.org/cern_ohl_s_v2.txt
Distributed WITHOUT ANY WARRANTY, see LICENSE
